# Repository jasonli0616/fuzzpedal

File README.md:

# fuzzpedal

A fuzz pedal controlled on your phone, using an ESP32.

A project for TEJ4M1.

See [schematic](./documentation/schematic.pdf) and [PCB design](./documentation/pcb.pdf), or open project in KiCad (use `./kicad` directory).

## Resources used

- Guitar pedal schematic from: https://www.instructables.com/DIY-Guitar-Pedal/

- ESP32 web server from: https://randomnerdtutorials.com/esp32-access-point-ap-web-server/

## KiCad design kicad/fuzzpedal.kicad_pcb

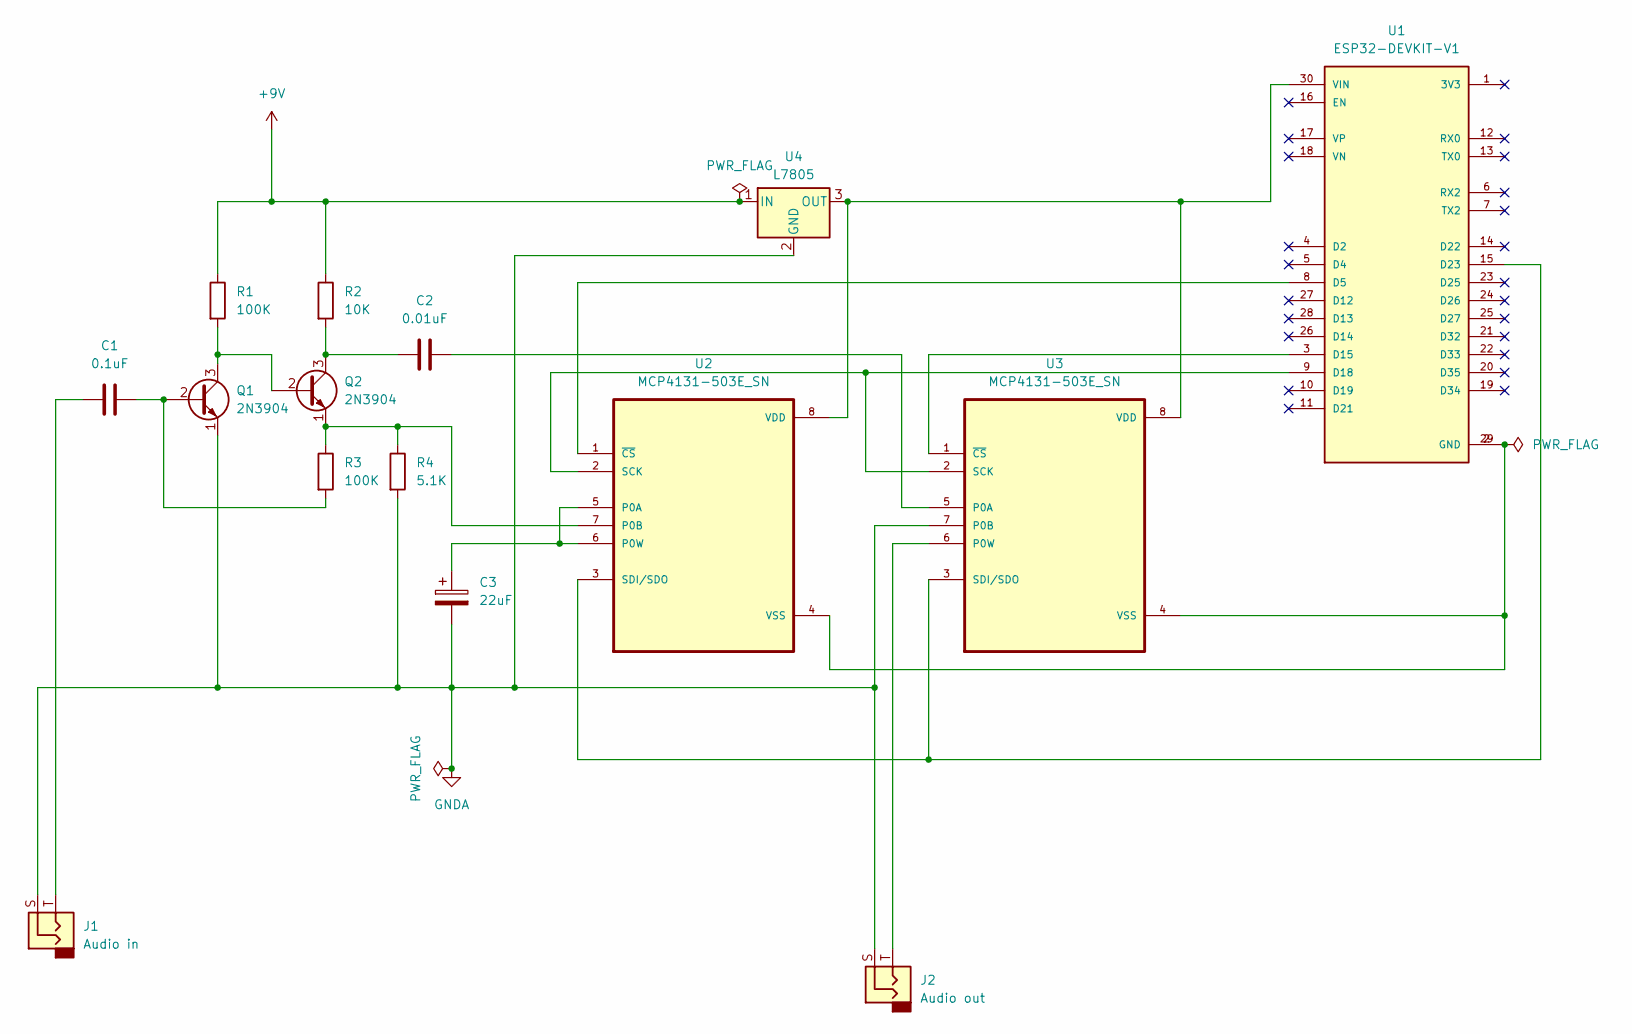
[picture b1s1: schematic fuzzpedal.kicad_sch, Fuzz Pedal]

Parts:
C1: 0.1uF; C_Disc_D3.8mm_W2.6mm_P2.50mm
C2: 0.01uF; C_Disc_D5.0mm_W2.5mm_P2.50mm
C3: 22uF; CP_Radial_D6.3mm_P2.50mm
J1: Audio in; PinHeader_1x02_P2.54mm_Vertical
J2: Audio out; PinHeader_1x02_P2.54mm_Vertical
Q1, Q2: 2N3904; TO-92_Inline
R1, R3: 100K; R_Axial_DIN0411_L9.9mm_D3.6mm_P12.70mm_Horizontal
R2: 10K; R_Axial_DIN0411_L9.9mm_D3.6mm_P12.70mm_Horizontal
R4: 5.1K; R_Axial_DIN0411_L9.9mm_D3.6mm_P12.70mm_Horizontal
U1: ESP32-DEVKIT-V1; MODULE_ESP32_DEVKIT_V1; PARTREV N/A
U2, U3: MCP4131-503E_SN; DIP-8_W7.62mm
U4: L7805; TO-220-3_Vertical

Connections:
+9V: R1.1, R2.1, U4.1 (IN); also elsewhere on the board
GNDA: C3.2, J1.S, J2.S, Q1.1 (E), R4.2, U3.7 (P0B), U4.2 (GND); also elsewhere on the board
unnamed: C1.1, J1.T
unnamed: C1.2, Q1.2 (B), R3.2
unnamed: Q1.3 (C), Q2.2 (B), R1.2
unnamed: C2.1, Q2.3 (C), R2.2
unnamed: Q2.1 (E), R3.1, R4.1, U2.7 (P0B)
unnamed: U1.8 (D5), U2.1 (~CS)
unnamed: U1.3 (D15), U3.1 (~CS)
unnamed: U1.9 (D18), U2.2 (SCK), U3.2 (SCK)
unnamed: U1.15 (D23), U2.3 (SDI/SDO), U3.3 (SDI/SDO)
unnamed: U1.30 (VIN), U2.8 (VDD), U3.8 (VDD), U4.3 (OUT)
unnamed: C3.1, U2.5 (P0A), U2.6 (P0W)
unnamed: U1.2 (GND), U1.29 (GND), U2.4 (VSS), U3.4 (VSS)
unnamed: C2.2, U3.5 (P0A)
unnamed: J2.T, U3.6 (P0W)

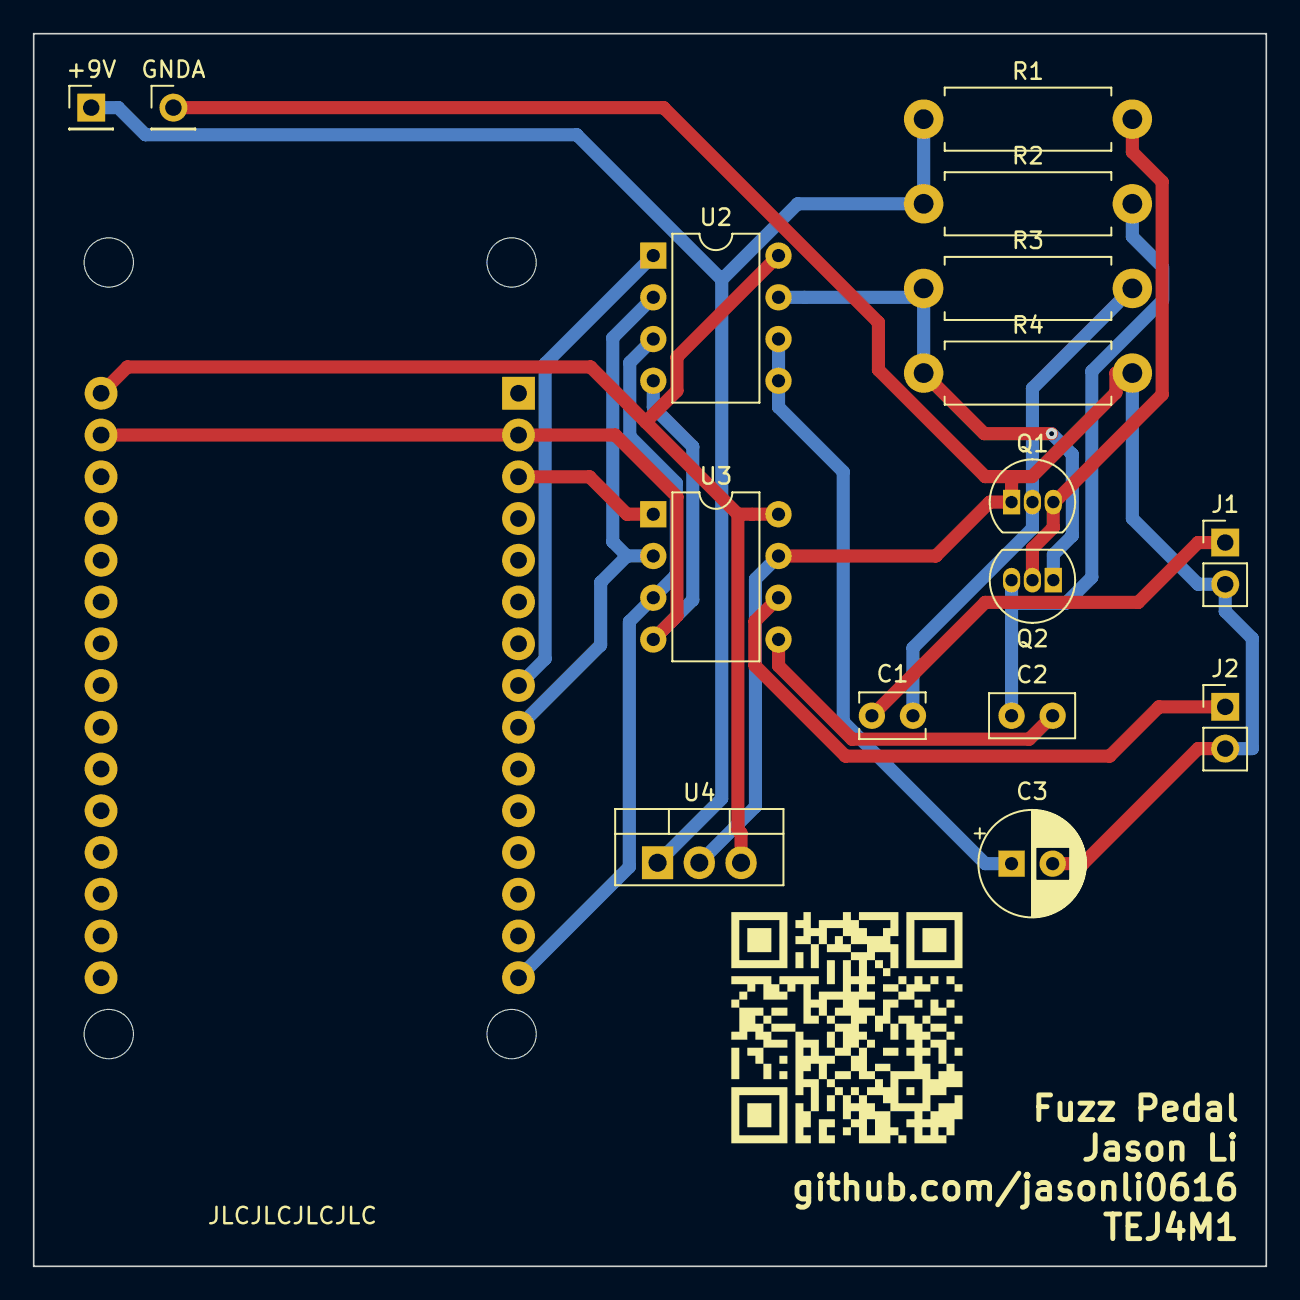
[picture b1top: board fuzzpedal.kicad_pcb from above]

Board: 2 copper layers, 75.0 x 75.0 mm, 17 parts (1 on the bottom side), 16 nets.

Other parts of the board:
+9V: PinHeader_1x01_P2.54mm_Vertical
GNDA: PinHeader_1x01_P2.54mm_Vertical

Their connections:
+9V: +9V.1; also elsewhere on the board
GNDA: GNDA.2; also elsewhere on the board

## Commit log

2023-12-23 Upload code and KiCad project
2023-12-23 Add KiCad footprints
2023-12-23 Add PCB images
